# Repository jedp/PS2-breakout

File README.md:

# PS/2 Breakout

Breakout board for PS/2 keyboard and mouse.

Converts 5v logic to 3v3.

Test points:

- TP1: PS/2 1, CLK 1
- TP2: PS/2 1, DATA 1
- TP3: PS/2 2, CLK 1
- TP4: PS/2 2, DATA 1
- TP9: PS/2 1, VCC
- TP10: PS/2 2, VCC

Supports Dualport on PS/2 1 when CLK and DATA are bridged.

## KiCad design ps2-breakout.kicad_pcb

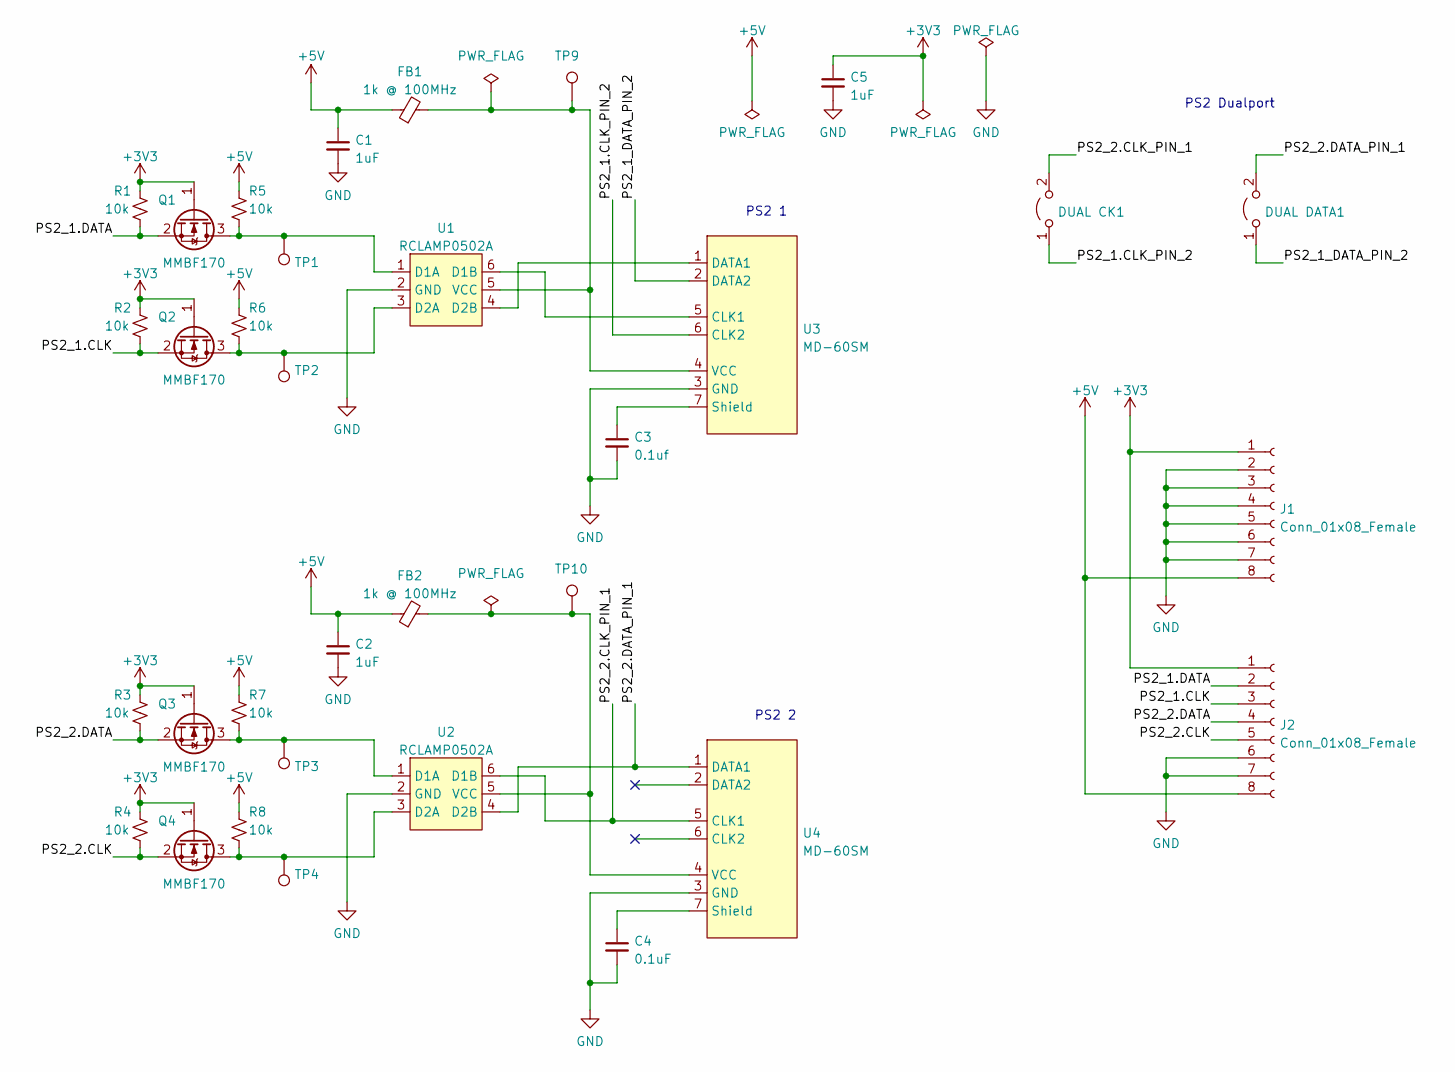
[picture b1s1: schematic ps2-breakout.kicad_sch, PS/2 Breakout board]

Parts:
C1, C2, C5: 1uF; C_0805_2012Metric
C3: 0.1uf; C_0603_1608Metric
C4: 0.1uF; C_0603_1608Metric
DUAL CK1: Jumper_2_Open; PinHeader_1x02_P2.54mm_Vertical
DUAL DATA1: Jumper_2_Open; PinHeader_1x02_P2.54mm_Vertical
FB1, FB2: 1k @ 100MHz; L_0603_1608Metric
J1, J2: Conn_01x08_Female; PinHeader_1x08_P2.54mm_Vertical
Q1, Q2, Q3, Q4: MMBF170; SOT-23
R1, R2, R3, R4, R5, R6, R7, R8: 10k; R_0603_1608Metric
TP1, TP2, TP3, TP4, TP9, TP10: TestPoint; TestPoint_Pad_D1.0mm
U1, U2: RCLAMP0502A; SOT-666
U3, U4: MD-60SM

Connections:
+3V3: C5.1, J1.1, J2.1, Q1.1 (G), Q2.1 (G), Q3.1 (G), Q4.1 (G), R1.1, R2.1, R3.1, R4.1
+5V: C1.1, C2.1, FB1.1, FB2.1, J1.8, J2.8, R5.1, R6.1, R7.1, R8.1
/PS2_1.CLK: J2.3, Q2.2 (S), R2.2
/PS2_1.CLK_PIN_2: DUAL CK1.1 (A), U3.6 (CLK2)
/PS2_1.DATA: J2.2, Q1.2 (S), R1.2
/PS2_1_DATA_PIN_2: DUAL DATA1.1 (A), U3.2 (DATA2)
/PS2_2.CLK: J2.5, Q4.2 (S), R4.2
/PS2_2.CLK_PIN_1: DUAL CK1.2 (B), U2.6 (D1B), U4.5 (CLK1)
/PS2_2.DATA: J2.4, Q3.2 (S), R3.2
/PS2_2.DATA_PIN_1: DUAL DATA1.2 (B), U2.4 (D2B), U4.1 (DATA1)
GND: C1.2, C2.2, C3.2, C4.2, C5.2, J1.2, J1.3, J1.4, J1.5, J1.6, J1.7, J2.6, J2.7, U1.2 (GND), U2.2 (GND), U3.3 (GND), U4.3 (GND)
unnamed: C3.1, U3.7 (Shield)
unnamed: C4.1, U4.7 (Shield)
unnamed: FB1.2, TP9.1, U1.5 (VCC), U3.4 (VCC)
unnamed: FB2.2, TP10.1, U2.5 (VCC), U4.4 (VCC)
unnamed: Q1.3 (D), R5.2, TP1.1, U1.1 (D1A)
unnamed: Q2.3 (D), R6.2, TP2.1, U1.3 (D2A)
unnamed: Q3.3 (D), R7.2, TP3.1, U2.1 (D1A)
unnamed: Q4.3 (D), R8.2, TP4.1, U2.3 (D2A)
unnamed: U1.4 (D2B), U3.1 (DATA1)
unnamed: U1.6 (D1B), U3.5 (CLK1)

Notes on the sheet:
PS2 1
PS2 Dualport
PS2 2

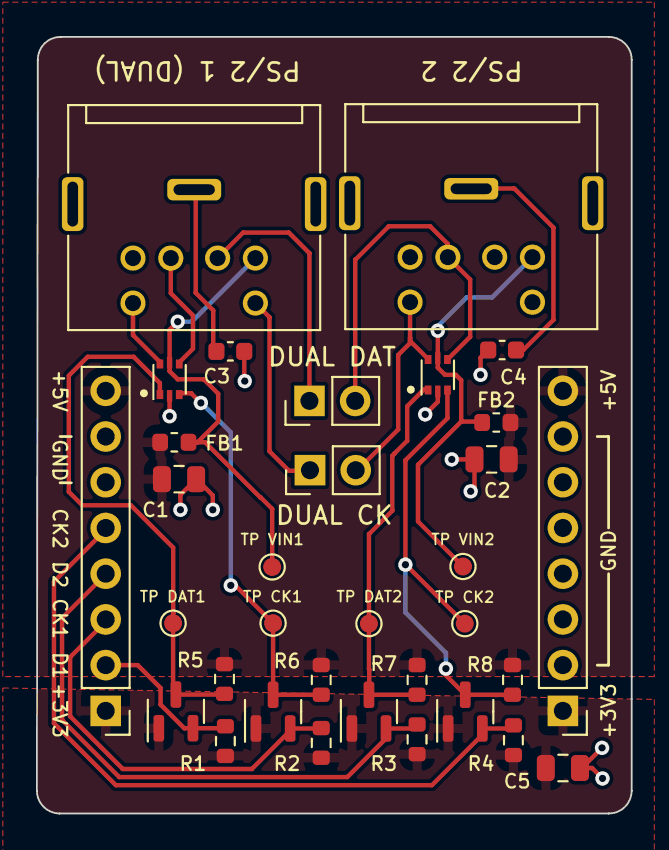
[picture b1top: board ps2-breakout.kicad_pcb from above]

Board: 2 copper layers, 33.0 x 43.1 mm, 33 parts (0 on the bottom side), 21 nets.

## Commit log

2023-12-26 PS/2 keyboard/mouse breakout board
2023-12-26 PCB image
2024-01-21 Fix RCLAMP0502 symbol and footprint
